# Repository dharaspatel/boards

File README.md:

# boards
repository for custom PCBs
### Sam and Dan were here

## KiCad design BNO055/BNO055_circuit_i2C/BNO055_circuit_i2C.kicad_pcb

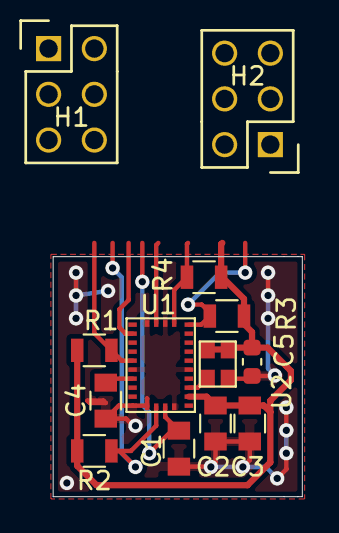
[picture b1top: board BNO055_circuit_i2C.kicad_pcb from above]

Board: 2 copper layers, 13.8 x 13.3 mm, 13 parts (0 on the bottom side), 11 nets.

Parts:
C1, C4: 100nF; C_0805_OEM
C2: 6.8nF; C_0805_OEM
C3: 120nF; C_0805_OEM
C5: 0.01u; C_0603_1608Metric
H1, H2: Header_2x3; Pin_Header_Straight_2x03
R1: Optional 10k; R_0805_OEM
R2: Pull-up 10k; R_0805_OEM
R3, R4: Rpull; R_0805_OEM
U1: BNO055
U2: ASDMB-xxxMHz; ASDK2-32.768KHZ-LR-T3

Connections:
COM3: H2.1, U1.17
GND: C1.2, C2.1, C3.1, C4.2, C5.1, H1.1, U1.2, U1.5, U1.6, U1.10, U1.16, U1.18, U1.25, U2.2
INT: H2.6, U1.14
unnamed: C4.1, U1.9
OptionalOSCinput: U1.27, U2.3
SCL: H2.3, R4.2, U1.19
SDA: H2.5, R3.2, U1.20
VDD: C1.1, H1.3, U1.3
VDDIO: C2.2, C3.2, C5.2, H1.5, R1.1, R2.1, R3.1, R4.1, U1.28, U2.1, U2.4
nBOOT_LOAD_PIN: H2.2, R2.2, U1.4
nRESET: H2.4, R1.2, U1.11

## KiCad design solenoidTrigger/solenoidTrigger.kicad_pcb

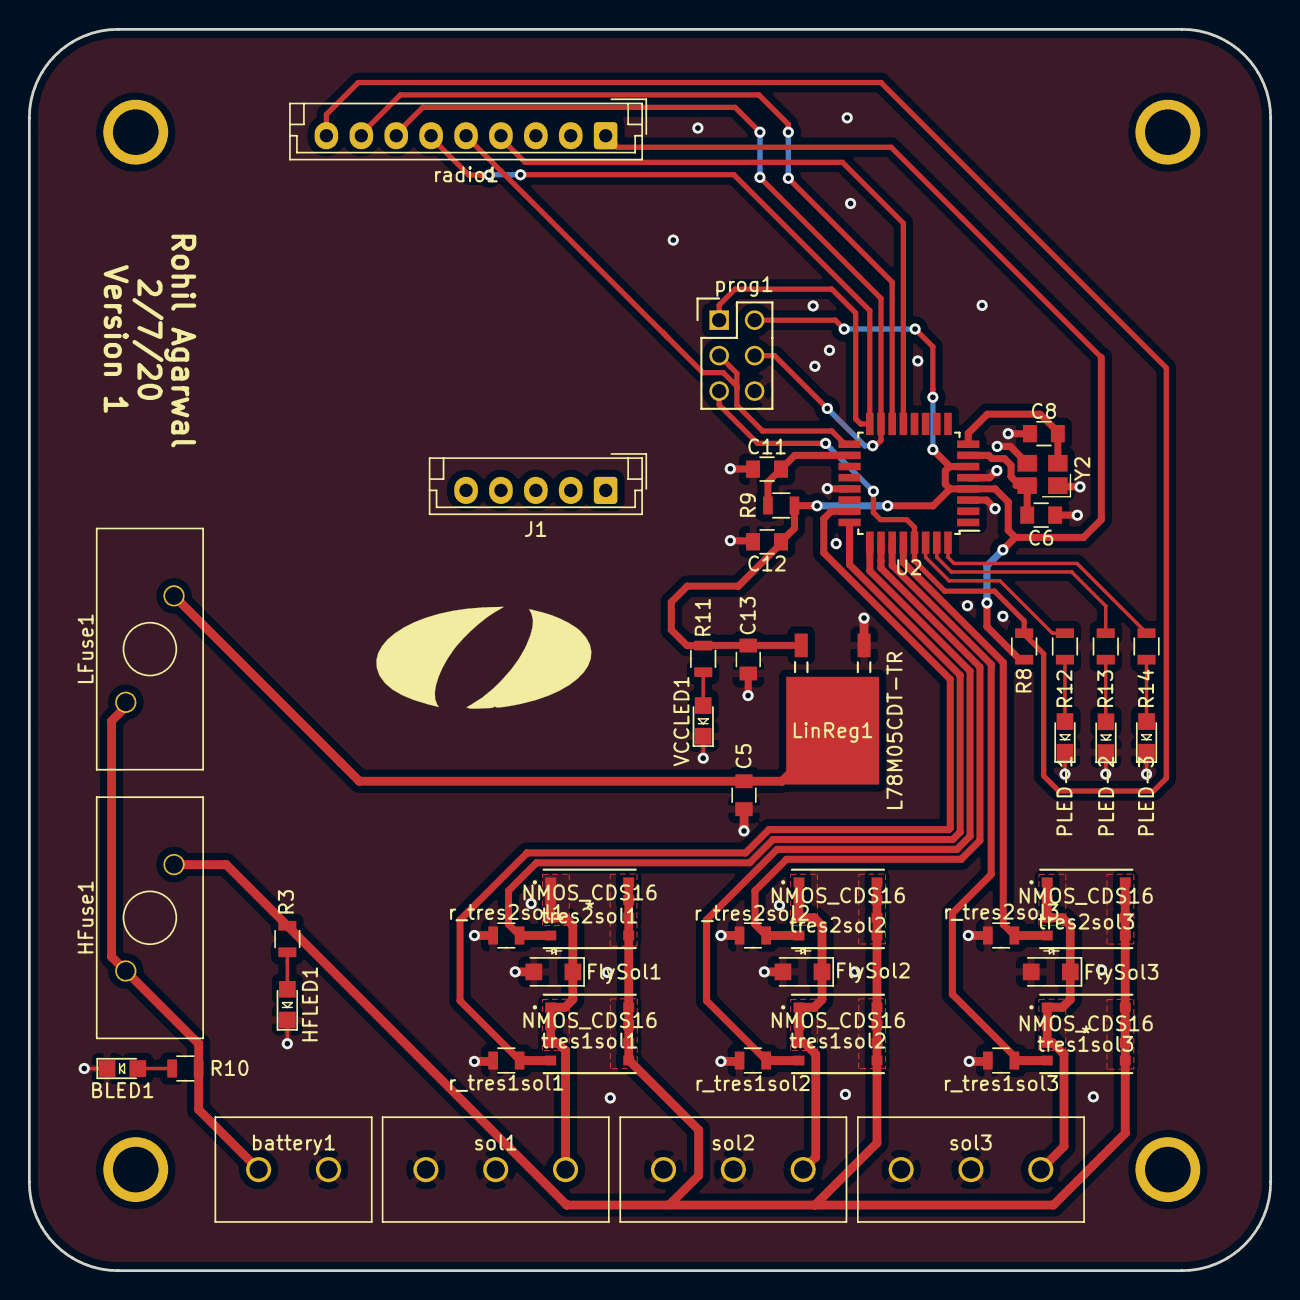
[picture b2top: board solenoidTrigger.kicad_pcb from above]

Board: 2 copper layers, 88.9 x 88.9 mm, 47 parts (0 on the bottom side), 32 nets.

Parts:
BLED1: LED_0805; LED_0805_OEM
C5: C_0.33uF; C_0805_OEM
C6, C8: C_30pF; C_0805_OEM
C11: C_100pF; C_0805_OEM
C12, C13: C_0.1uF; C_0805_OEM
FlySol1, FlySol2, FlySol3: SS110LW; D_SOD-123W_OEM
HFLED1: LED_0805; LED_0805_OEM
HFuse1: 01530008Z
J1: NoConnectRadio; JST_EH_B5B-EH-A_1x05_P2.50mm_Vertical
LFuse1: 01530008Z
LinReg1: L78M05CDT-TR
PLED-1, PLED-2, PLED-3: LED_0805; LED_0805_OEM
R3, R10: R_499; R_0805_OEM
R8: R_10K; R_0805_OEM
R9: R_100; R_0805_OEM
R11, R12, R13, R14: R_200; R_0805_OEM
U2: ATmega328P-AU; TQFP-32_7x7mm_P0.8mm
VCCLED1: LED_0805; LED_0805_OEM
Y2: Crystal_SMD; Crystal_SMD_FA238
battery1: OSTTC02
prog1: CONN_02X03; Pin_Header_Straight_2x03
r_tres1sol1, r_tres1sol2, r_tres1sol3, r_tres2sol1, r_tres2sol2, r_tres2sol3: R_1K; R_0805_OEM
radio1: Conn_01x09_Female; JST_EH_B9B-EH-A_1x09_P2.50mm_Vertical
sol1, sol2, sol3: OSTTC03; OSTTC030162
tres1sol1, tres1sol2, tres1sol3, tres2sol1, tres2sol2, tres2sol3: NMOS_CDS16; CSD16322Q5

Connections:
/12V_Low: C5.2, LFuse1.1, LinReg1.3
/12V_Solenoid1: FlySol1.1, sol1.1, tres1sol1.1, tres1sol1.2, tres1sol1.3, tres2sol1.1, tres2sol1.2, tres2sol1.3
/12V_Solenoid2: FlySol2.1, sol2.1, tres1sol2.1, tres1sol2.2, tres1sol2.3, tres2sol2.1, tres2sol2.2, tres2sol2.3
/12V_Solenoid3: FlySol3.1, sol3.1, tres1sol3.1, tres1sol3.2, tres1sol3.3, tres2sol3.1, tres2sol3.2, tres2sol3.3
/12V_Switch: HFuse1.1, R3.1, tres1sol1.5, tres1sol1.6, tres1sol1.7, tres1sol1.8, tres1sol2.5, tres1sol2.6, tres1sol2.7, tres1sol2.8, tres1sol3.5, tres1sol3.6, tres1sol3.7, tres1sol3.8, tres2sol1.5, tres2sol1.6, tres2sol1.7, tres2sol1.8, tres2sol2.5, tres2sol2.6, tres2sol2.7, tres2sol2.8, tres2sol3.5, tres2sol3.6, tres2sol3.7, tres2sol3.8
/CS: U2.14, radio1.8
/G0(IRQ): U2.13, radio1.4
/MISO: U2.16, prog1.1, radio1.6
/MOSI: U2.15, prog1.4, radio1.7
/PLED1: R12.1, U2.30
/PLED2: R13.1, U2.31
/PLED3: R14.1, U2.32
/RESET: R8.1, U2.29, prog1.5, radio1.9
/SCK: U2.17, prog1.3, radio1.5
/Source(12V): HFuse1.2, LFuse1.2, R10.1, battery1.1
/ctrl_pin_1-1: U2.23, r_tres1sol1.1, tres1sol1.4
/ctrl_pin_1-2: U2.24, r_tres2sol1.1, tres2sol1.4
/ctrl_pin_2-1: U2.25, r_tres1sol2.1, tres1sol2.4
/ctrl_pin_2-2: U2.26, r_tres2sol2.1, tres2sol2.4
/ctrl_pin_3-1: U2.27, r_tres1sol3.1, tres1sol3.4
/ctrl_pin_3-2: U2.28, r_tres2sol3.1, tres2sol3.4
GND: BLED1.1, C5.1, C6.2, C8.2, C11.1, C12.2, C13.2, FlySol1.2, FlySol2.2, FlySol3.2, HFLED1.1, LinReg1.1, PLED-1.1, PLED-2.1, PLED-3.1, U2.3, U2.5, U2.21, VCCLED1.1, Y2.2, Y2.4, battery1.2, prog1.6, r_tres1sol1.2, r_tres1sol2.2, r_tres1sol3.2, r_tres2sol1.2, r_tres2sol2.2, r_tres2sol3.2, radio1.2, sol1.2, sol1.3, sol2.2, sol2.3, sol3.2, sol3.3
unnamed: BLED1.2, R10.2
unnamed: C6.1, U2.7, Y2.3
unnamed: C8.1, U2.8, Y2.1
unnamed: C11.2, R9.1, U2.18
unnamed: HFLED1.2, R3.2
unnamed: PLED-1.2, R12.2
unnamed: PLED-2.2, R13.2
unnamed: PLED-3.2, R14.2
unnamed: R11.2, VCCLED1.2
VCC: C12.1, C13.1, LinReg1.2, R8.2, R9.2, R11.1, U2.4, U2.6, prog1.2, radio1.1

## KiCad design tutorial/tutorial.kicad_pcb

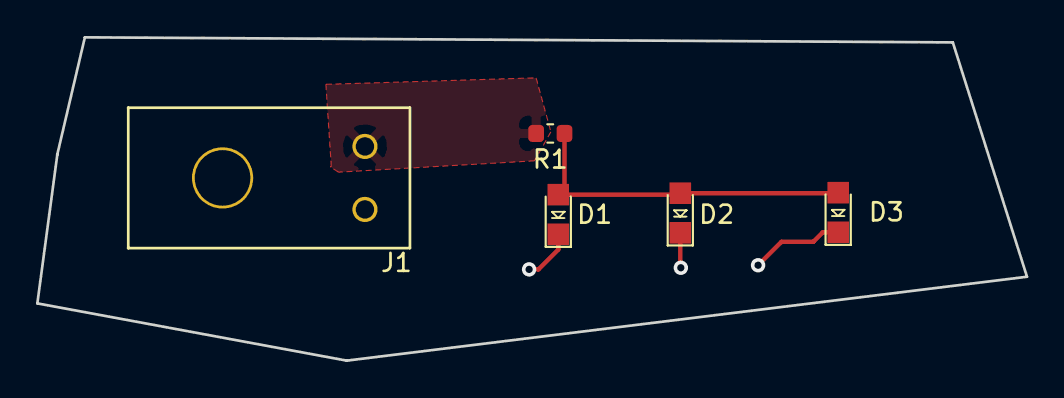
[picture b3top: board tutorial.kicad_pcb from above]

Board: 2 copper layers, 55.0 x 18.0 mm, 5 parts (0 on the bottom side), 3 nets.

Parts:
D1, D2, D3: LED_0805; LED_0805_OEM
J1: UF_2_RA; Ultrafit_2_RA
R1: R_0; R_0603_1608Metric

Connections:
/12V: J1.1, R1.2
GND: D1.1, D2.1, D3.1, J1.2
unnamed: D1.2, D2.2, D3.2, R1.1

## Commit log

2019-10-01 added kicad tutorial board
2019-10-04 first rendor of bms: reverse protection, atmega, shockky
2019-10-04 added basic schematic
2019-10-07 changed resistor label
2019-10-21 As Of Oct 21
2019-10-22 After Oct 21 meeting
2019-10-22 temperature sensing
2019-10-30 As of Oct 30, documented with to do list and questions. When these are resolved, I think we can move on to the next step (probably laying out the actual PCB footprints)
2019-11-01 As of Nov 1, started adding LEDs
2019-11-02 passive charge redistribution and temp monitoring
2019-11-08 As of Nov 8, PCB schematic almost done
2019-11-12 started charging and balancing
2019-11-15 saved bms
2019-11-15 post-design review 11/15
2019-11-15 charging circuit
2019-11-19 Almost ready to start actual layout and traces
2019-11-22 Updated with no errors
2019-11-25 a little bit of progress
2019-11-28 Nov 28, have reduced trace overlaps
2019-12-02 started adding traces
2019-12-02 Almost done with first version of laying down traces
2019-12-03 created 3 new parts and updated these in the schematic
2019-12-04 Aside from the fact that the fuse and switch footprints need to be added, all the traces for the PCB have been laid out!
2019-12-10 test
2019-12-10 added atsamd21
2019-12-13 12/12
2019-12-13 second try
2019-12-13 moved 3 pin connector
2019-12-15 Created part for fuse reciprocal, deleted most traces, laying out board again to improve organization and performance
2019-12-15 Continued laying out components on board
2019-12-15 continued moving around components
2019-12-18 moved all components into what seems to be resonable positions, waiting for confirmation from Will before adding traces/vias
2019-12-18 moved linear regulator closer to atmega
2019-12-18 moved around oscillator
2019-12-19 moved purple to left side of atmega
2019-12-19 continued moving components based on Will's feedback
2020-01-02 bms updates
2020-01-04 added flyback diode
2020-01-04 added bms2 with simplified, final charging and discharging circuits
2020-01-07 charge shunting and connectors
2020-01-07 I think I have finished the final schematic, added flybacks and second fuse
2020-01-07 deleted one flyback per solenoid
2020-01-07 integration of connectors, power flags, thermocouples
2020-01-08 final schematic and layout prior to traces dependent on Will's approval
2020-01-08 hopefully final board prior to layout of traces
2020-01-10 thermal monitoring and eFuse safety
2020-01-16 global deletion of all tracks so I can replace all of them
2020-01-16 placed down about half the traces
2020-01-17 first pass done pending approval
2020-01-30 added another LED, changed some pins, changed flybacks
2020-01-30 removed switch
2020-01-31 moved components away from mounting holes
2020-01-31 labeling
2020-01-31 added back 3rd solenoid
2020-02-04 starting adding fills
2020-02-07 finished unless i want to add a picture to the board
2020-02-07 added name, data, and version number
2020-02-07 DONE WITH TEST BOARD
2020-02-14 MAX1648 charging chip!
2020-02-28 C and R values for charging circuit
2020-03-04 all footprints addedgit add .git add .!
2020-10-16 Move recovery board files to recovery repo
2020-10-23 Add BNO055
2020-12-15 redesign BNO055 breakout, except for small changes
2020-12-20 finish optimizing BNO055 layout: Version 3
2020-12-20 add MPL3115 barometer schematic and layout
2021-01-25 fabrication outputs to JLC
2021-04-19 fab outputs

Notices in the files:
parts and their libraries:
Copyright 2016 Accelerated Designs. All rights reserved.
